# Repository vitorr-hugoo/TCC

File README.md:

# Estacao meteorologica — TCC

Este repositorio separa as fontes do produto, a documentacao duradoura e as
ferramentas de apoio. Arquivos gerados localmente ficam em `work/` e nao fazem
parte do historico Git.

| Area | Conteudo |
| --- | --- |
| `firmware/` | Firmware STM32, gateway ESP32, testes e configuracoes do produto. |
| `hardware/` | Projeto KiCad, bibliotecas locais e pacotes de fabricacao por versao. |
| `docs/` | Material do TCC, referencias e registros de engenharia. |
| `tools/` | Scripts reprodutiveis para hardware, documentos e automacao. |
| `work/` | Caches, renderizacoes e resultados locais descartaveis. |

Consulte os READMEs de cada area antes de alterar caminhos ou executar scripts.

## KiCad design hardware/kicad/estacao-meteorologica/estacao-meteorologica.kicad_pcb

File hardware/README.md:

# Hardware

O projeto principal esta em `kicad/estacao-meteorologica/`. Abra o arquivo
`estacao-meteorologica.kicad_pro` no KiCad. As folhas hierarquicas ficam em
`sheets/` e as bibliotecas locais do projeto ficam em `libraries/`.

As tabelas de simbolos e footprints usam caminhos relativos para
`../../libraries`, de modo que o projeto permanece portatil apos o clone.
`kicad/legacy/` preserva folhas antigas que nao fazem parte da hierarquia ativa.
Pacotes de fabricacao aprovados devem ser organizados por versao em `releases/`.

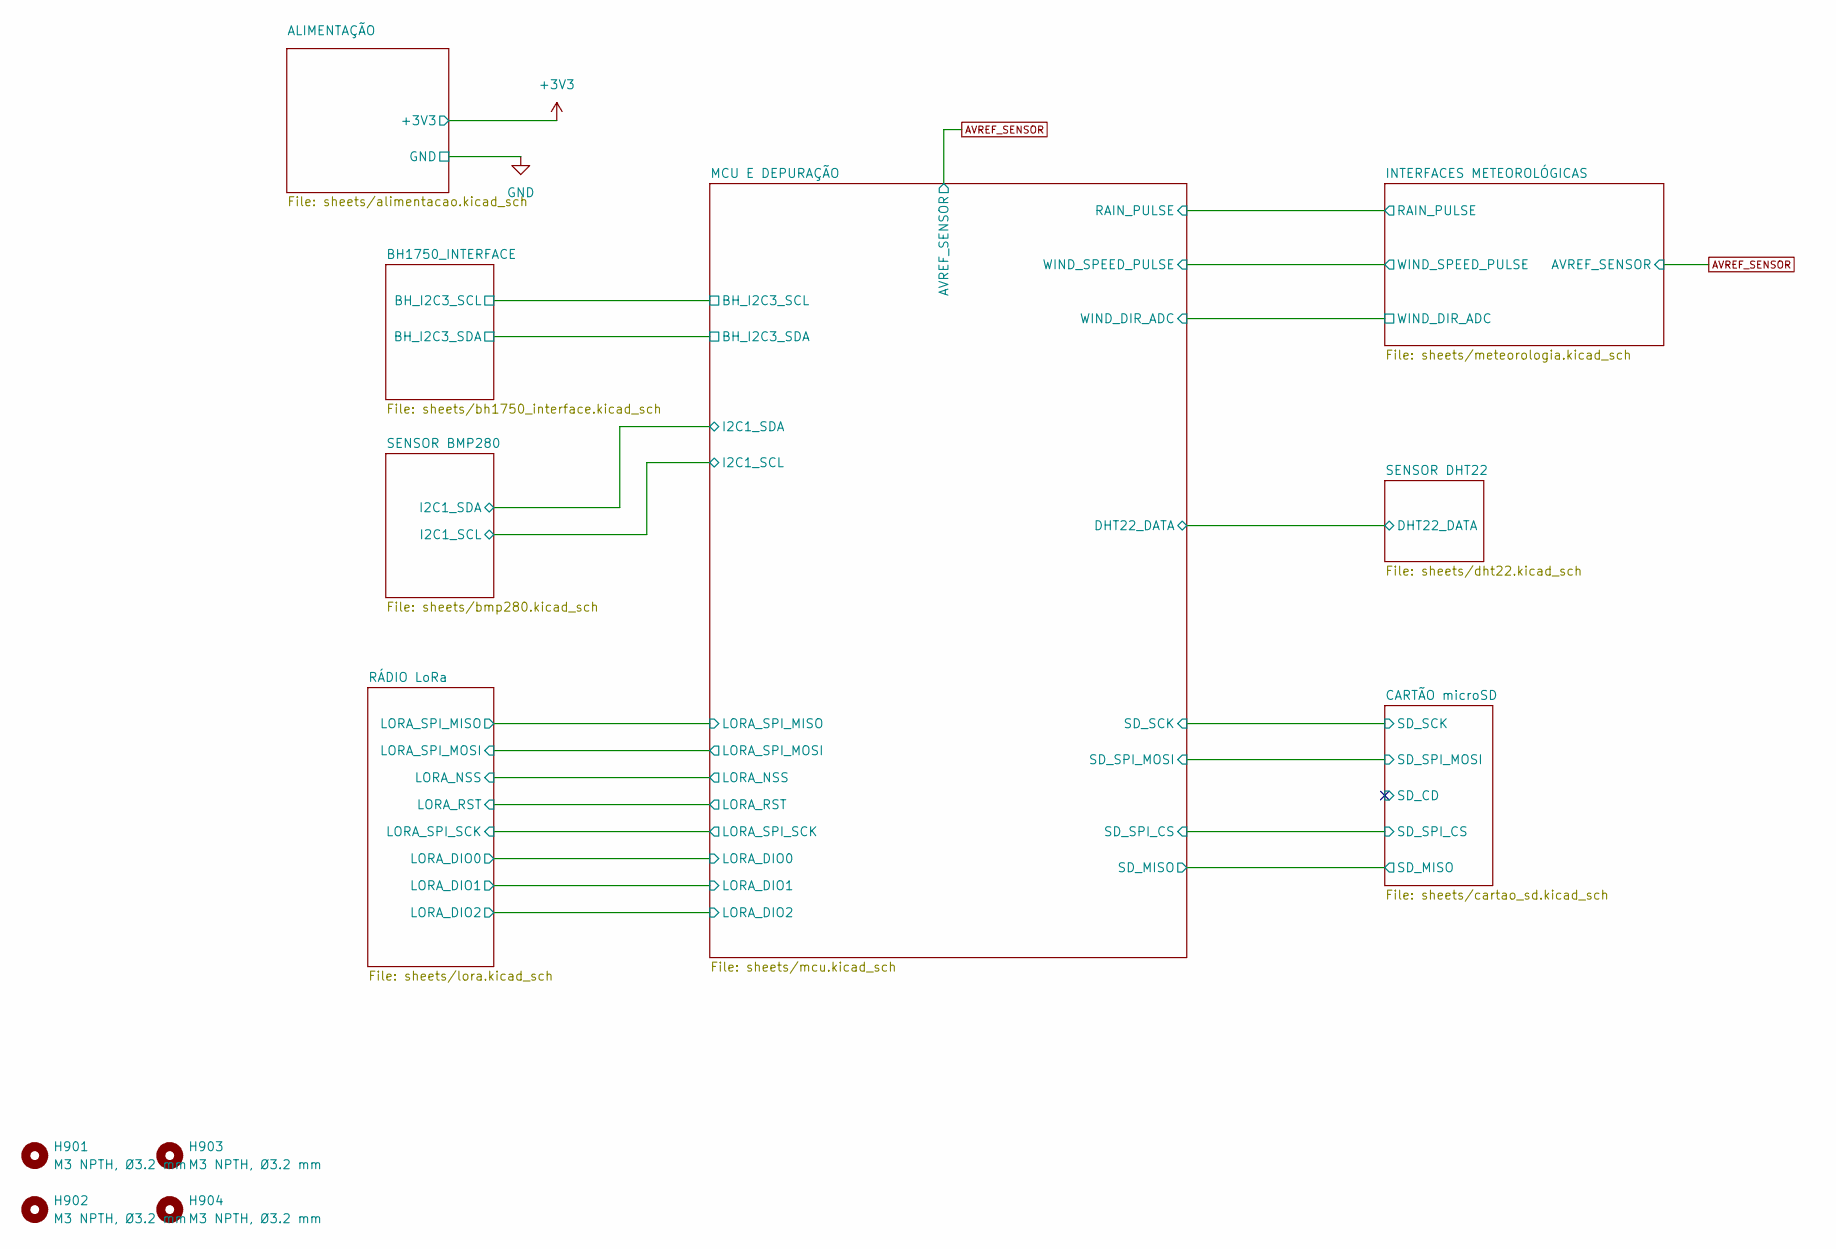
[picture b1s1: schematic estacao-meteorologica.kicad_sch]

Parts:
H901, H902, H903, H904: M3 NPTH, Ø3.2 mm; MountingHole_3.2mm_M3; MPN N/A — recurso mecânico da PCB; LCSC N/A

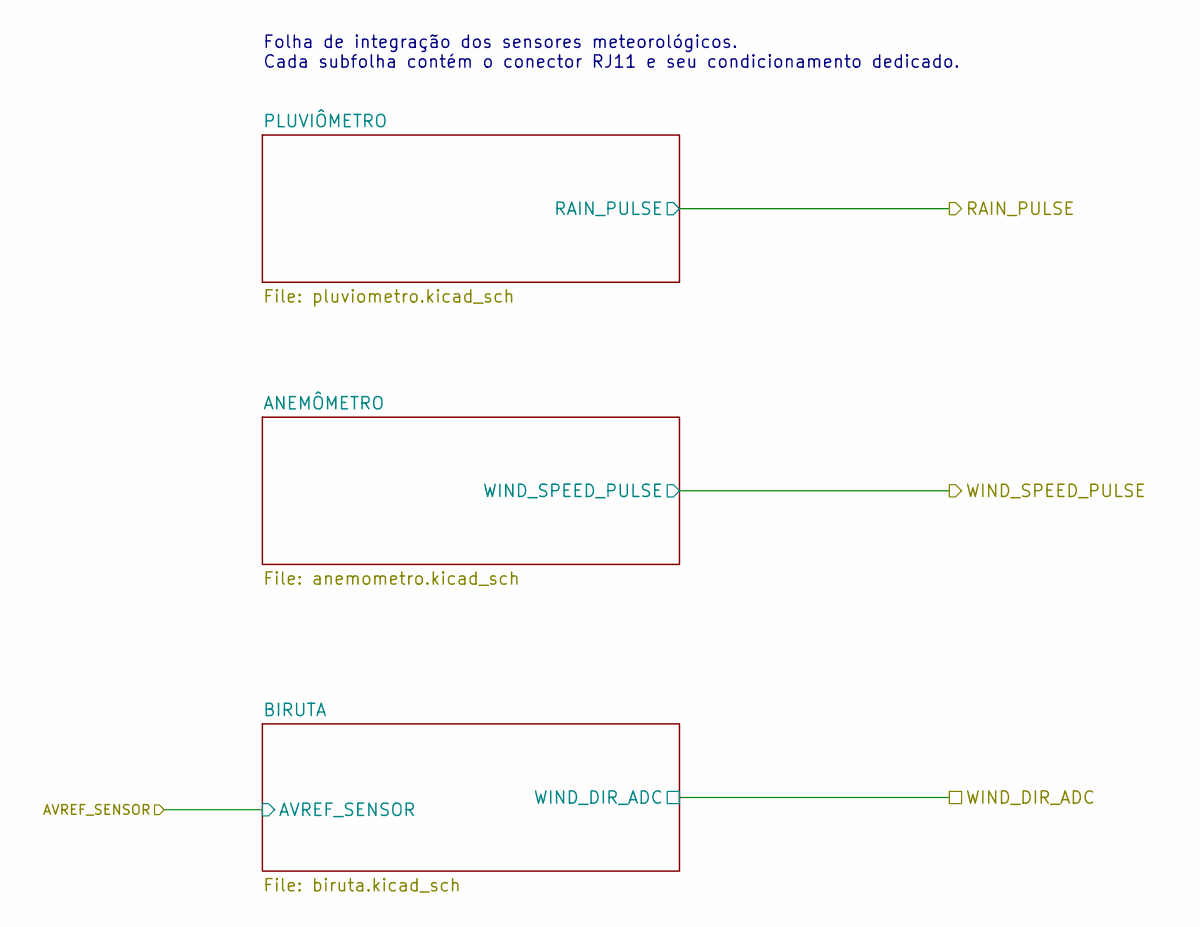
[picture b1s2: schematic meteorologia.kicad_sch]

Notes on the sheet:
Folha de integração dos sensores meteorológicos. Cada subfolha contém o conector RJ11 e seu condicionamento dedicado.

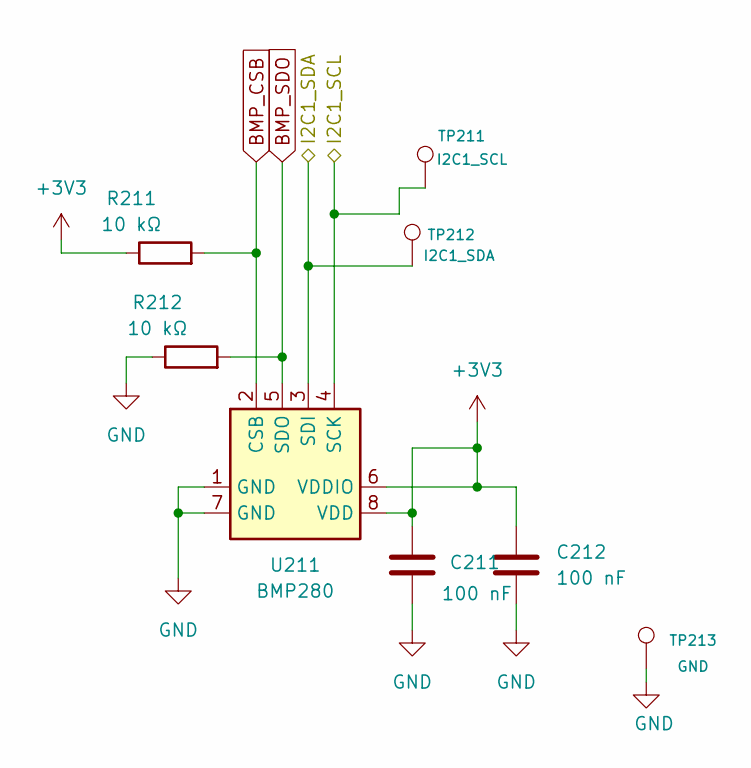
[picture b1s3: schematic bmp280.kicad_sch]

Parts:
C211, C212: 100 nF; C_0603_1608Metric; MPN CC0603KRX7R9BB104; LCSC C14663
R211, R212: 10 kΩ; R_0603_1608Metric; MPN 0603WAF1002T5E; LCSC C25804
TP211: I2C1_SCL; TestPoint_Pad_D1.0mm; MPN N/A - elemento de cobre da PCB; LCSC N/A
TP212: I2C1_SDA; TestPoint_Pad_D1.0mm; MPN N/A - elemento de cobre da PCB; LCSC N/A
TP213: GND; TestPoint_Pad_D1.0mm; MPN N/A - elemento de cobre da PCB; LCSC N/A
U211: BMP280; Bosch_LGA-8_2x2.5mm_P0.65mm_ClockwisePinNumbering; MPN BMP280; LCSC C83291

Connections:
+3V3: C211.1, C212.1, R211.1, U211.6 (VDDIO), U211.8 (VDD); also elsewhere on the board
/MCU E DEPURAÇÃO/I2C1_SCL: TP211.1, U211.4 (SCK); also elsewhere on the board
/MCU E DEPURAÇÃO/I2C1_SDA: TP212.1, U211.3 (SDI); also elsewhere on the board
BMP_CSB: R211.2, U211.2 (CSB)
BMP_SDO: R212.2, U211.5 (SDO)
GND: C211.2, C212.2, R212.1, TP213.1, U211.1 (GND), U211.7 (GND); also elsewhere on the board

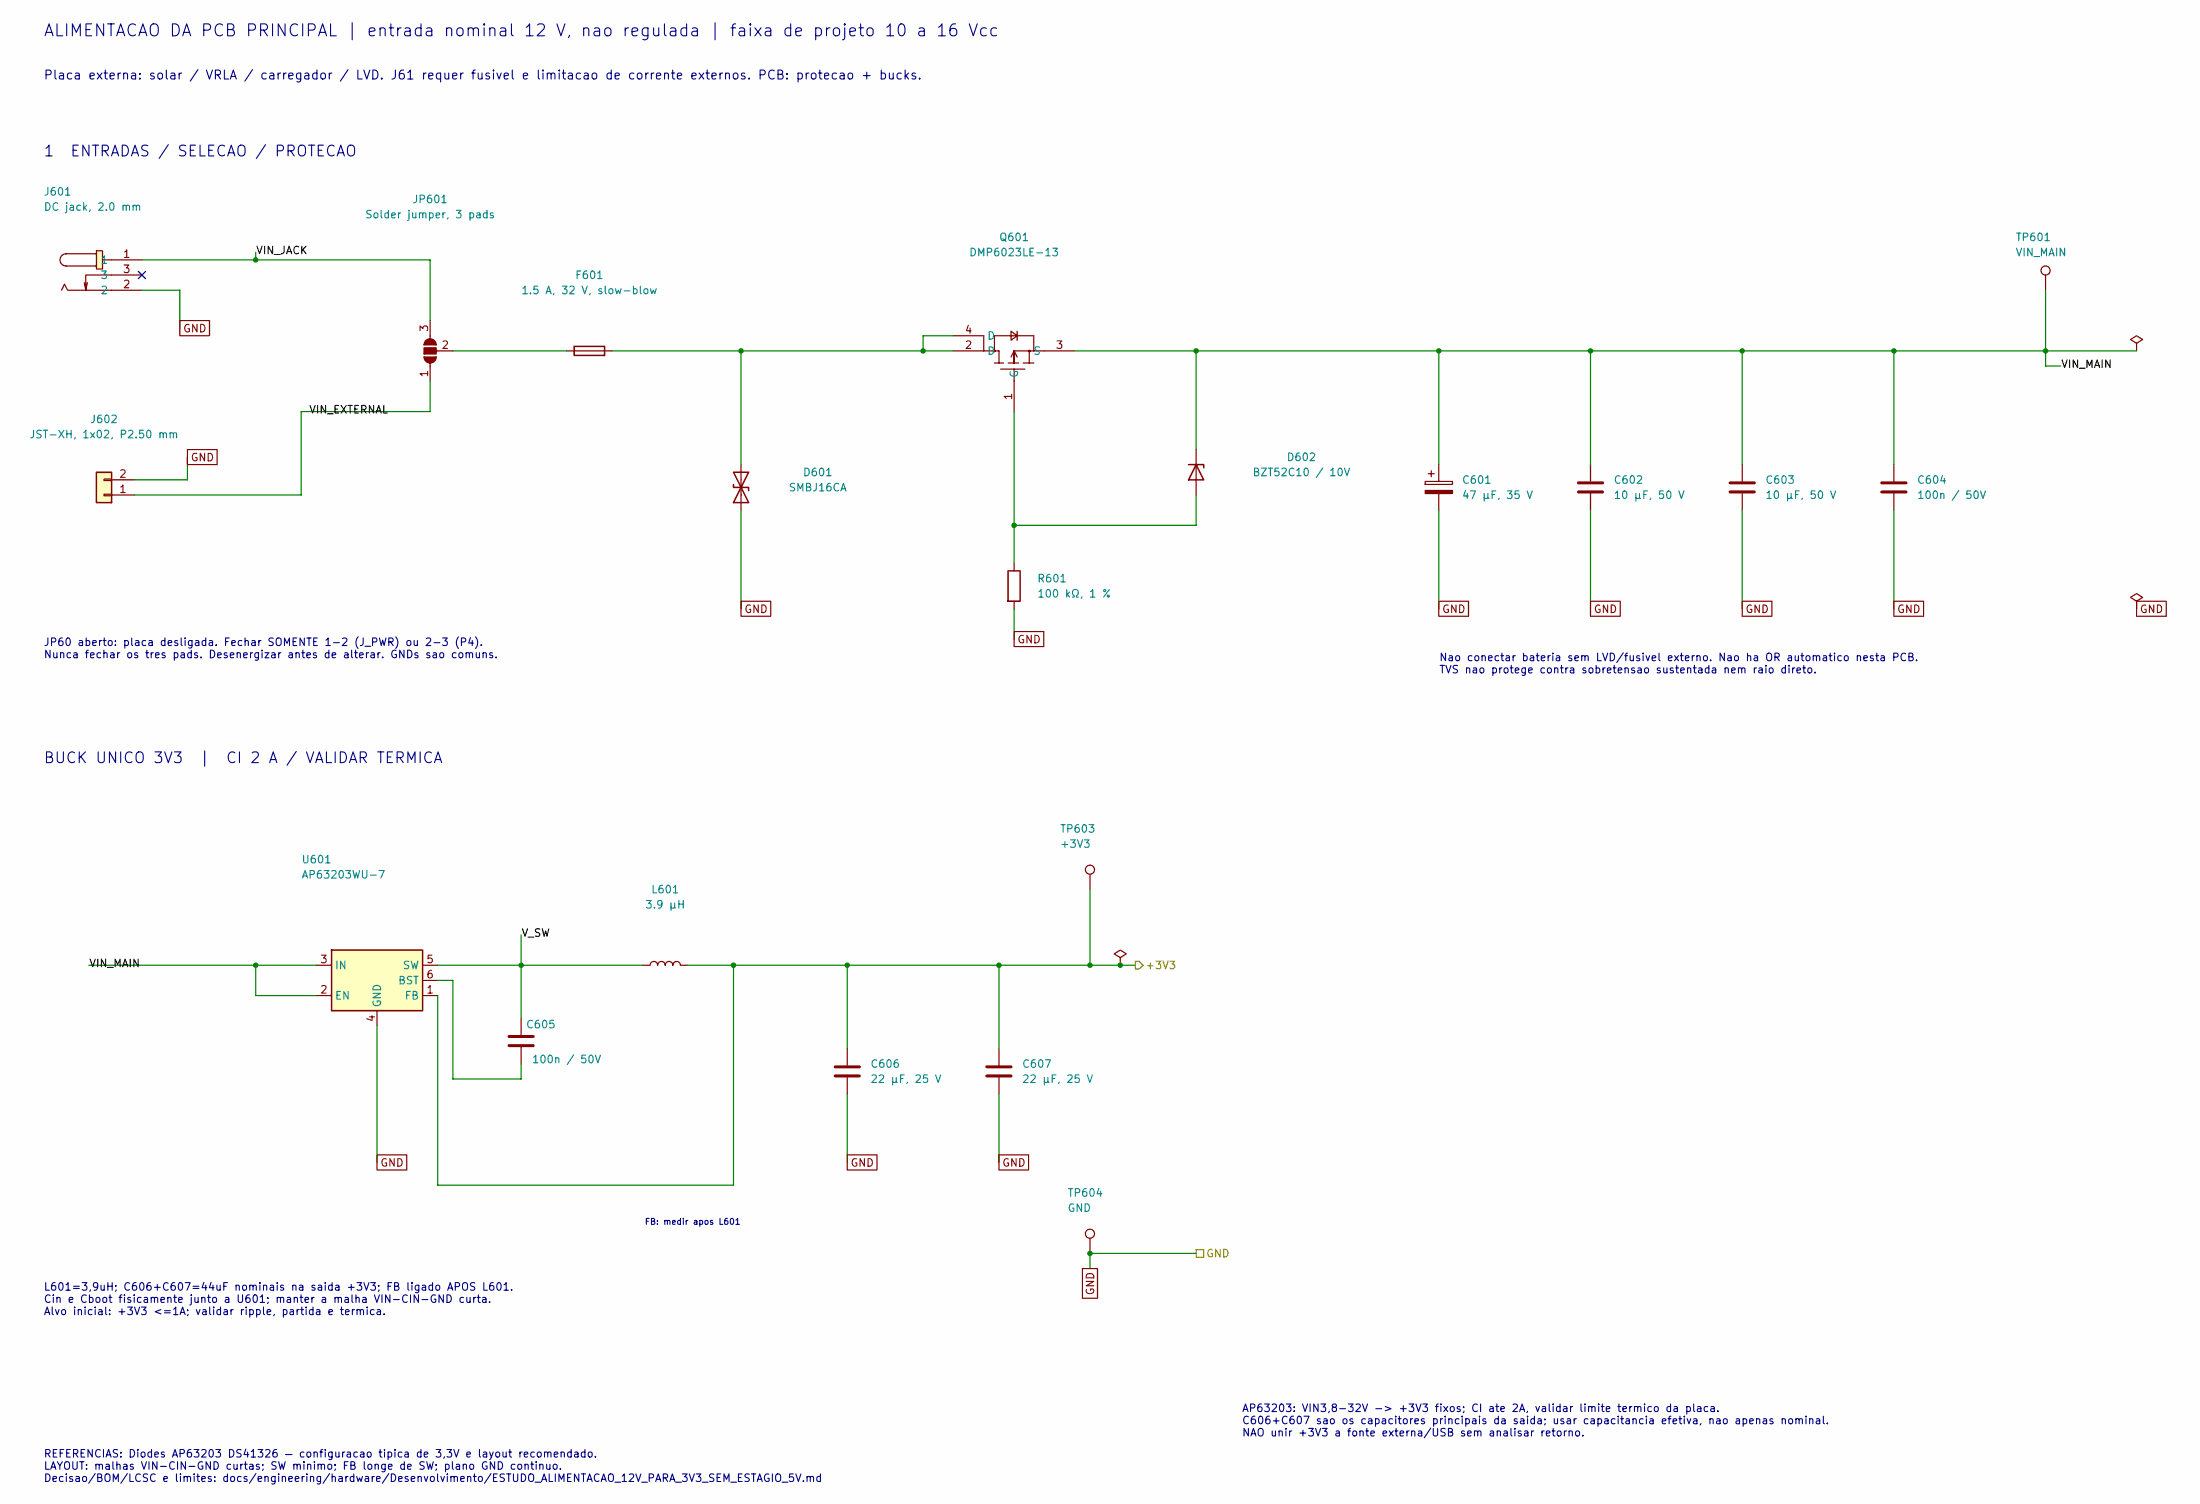
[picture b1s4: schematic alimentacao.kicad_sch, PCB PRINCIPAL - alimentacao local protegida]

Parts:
C601: 47 µF, 35 V; CP_Elec_6.3x5.8; MPN UWT1V470MCL1GS; LCSC C87068
C602, C603: 10 µF, 50 V; C_1206_3216Metric; MPN CL31A106KBHNNNE; LCSC C13585
C604, C605: 100n / 50V; C_0603_1608Metric; MPN CC0603KRX7R9BB104; LCSC C14663
C606, C607: 22 µF, 25 V; C_1206_3216Metric; MPN CL31A226KAHNNNE; LCSC C12891
D601: SMBJ16CA; D_SMB; MPN SMBJ16CA; LCSC C3001977
D602: BZT52C10 / 10V; D_SOD-123; MPN BZT52C10; LCSC C19077408
F601: 1.5 A, 32 V, slow-blow; Fuse_1206_3216Metric; MPN S1206-S-1.5A; LCSC C553929
J601: DC jack, 2.0 mm; DC-IN-TH_DC-005-2.0_C22459640; MPN DC-005-2.0; LCSC C22459640
J602: JST-XH, 1x02, P2.50 mm; JST_XH_B2B-XH-A_1x02_P2.50mm_Vertical; MPN B2B-XH-A(LF)(SN); LCSC C158012
JP601: Solder jumper, 3 pads; SolderJumper-3_P2.0mm_Open_TrianglePad1.0x1.5mm_NumberLabels; MPN N/A - elemento de cobre da PCB; LCSC N/A
L601: 3.9 µH; L_APV_ANR5040; MPN ANR5040T3R9M; LCSC C7427132
Q601: DMP6023LE-13; SOT-223-4_L6.5-W3.5-P2.30-LS7.0-BR; MPN DMP6023LE-13; LCSC C154901
R601: 100 kΩ, 1 %; R_0603_1608Metric; MPN 0603WAF1003T5E; LCSC C25803
TP601: VIN_MAIN; TestPoint_Pad_D1.0mm; MPN N/A - elemento de cobre da PCB; LCSC N/A
TP603: +3V3; TestPoint_Pad_D1.0mm; MPN N/A - elemento de cobre da PCB; LCSC N/A
TP604: GND; TestPoint_Pad_D1.0mm; MPN N/A - elemento de cobre da PCB; LCSC N/A
U601: AP63203WU-7; TSOT-23-6; MPN AP63203WU-7; LCSC C780769

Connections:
+3V3: C606.1, C607.1, L601.2, TP603.1, U601.1 (FB); also elsewhere on the board
/ALIMENTAÇÃO/VIN_EXTERNAL: J602.1, JP601.1 (A)
/ALIMENTAÇÃO/VIN_JACK: J601.1, JP601.3 (B)
/ALIMENTAÇÃO/VIN_MAIN: C601.1, C602.1, C603.1, C604.1, D602.1 (K), Q601.3 (S), TP601.1, U601.2 (EN), U601.3 (IN)
/ALIMENTAÇÃO/V_SW: C605.2, L601.1, U601.5 (SW)
GND: C601.2, C602.2, C603.2, C604.2, C606.2, C607.2, D601.1 (A1), J601.2, J602.2, R601.2, TP604.1, U601.4 (GND); also elsewhere on the board
unnamed: D601.2 (A2), F601.2, Q601.2 (D), Q601.4 (D)
unnamed: D602.2 (A), Q601.1 (G), R601.1
unnamed: F601.1, JP601.2 (C)
unnamed: C605.1, U601.6 (BST)

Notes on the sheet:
ALIMENTACAO DA PCB PRINCIPAL | entrada nominal 12 V, nao regulada | faixa de projeto 10 a 16 Vcc
L601=3,9uH; C606+C607=44uF nominais na saida +3V3; FB ligado APOS L601. Cin e Cboot fisicamente junto a U601; manter a malha VIN-CIN-GND curta. Alvo inicial: +3V3 <=1A; validar ripple, partida e termica.
AP63203: VIN3,8-32V -> +3V3 fixos; CI ate 2A, validar limite termico da placa. C606+C607 sao os capacitores principais da saida; usar capacitancia efetiva, nao apenas nominal. NAO unir +3V3 a fonte externa/USB sem analisar retorno.
Placa externa: solar / VRLA / carregador / LVD. J61 requer fusivel e limitacao de corrente externos. PCB: protecao + bucks.
1 ENTRADAS / SELECAO / PROTECAO
REFERENCIAS: Diodes AP63203 DS41326 — configuracao tipica de 3,3V e layout recomendado. LAYOUT: malhas VIN-CIN-GND curtas; SW minimo; FB longe de SW; plano GND continuo. Decisao/BOM/LCSC e limites: docs/engineering/hardware/Desenvolvimento/ESTUDO_ALIMENTACAO_12V_PARA_3V3_SEM_ESTAGIO_5V.md
JP60 aberto: placa desligada. Fechar SOMENTE 1-2 (J_PWR) ou 2-3 (P4). Nunca fechar os tres pads. Desenergizar antes de alterar. GNDs sao comuns.
Nao conectar bateria sem LVD/fusivel externo. Nao ha OR automatico nesta PCB. TVS nao protege contra sobretensao sustentada nem raio direto.
BUCK UNICO 3V3 | CI 2 A / VALIDAR TERMICA
FB: medir apos L601

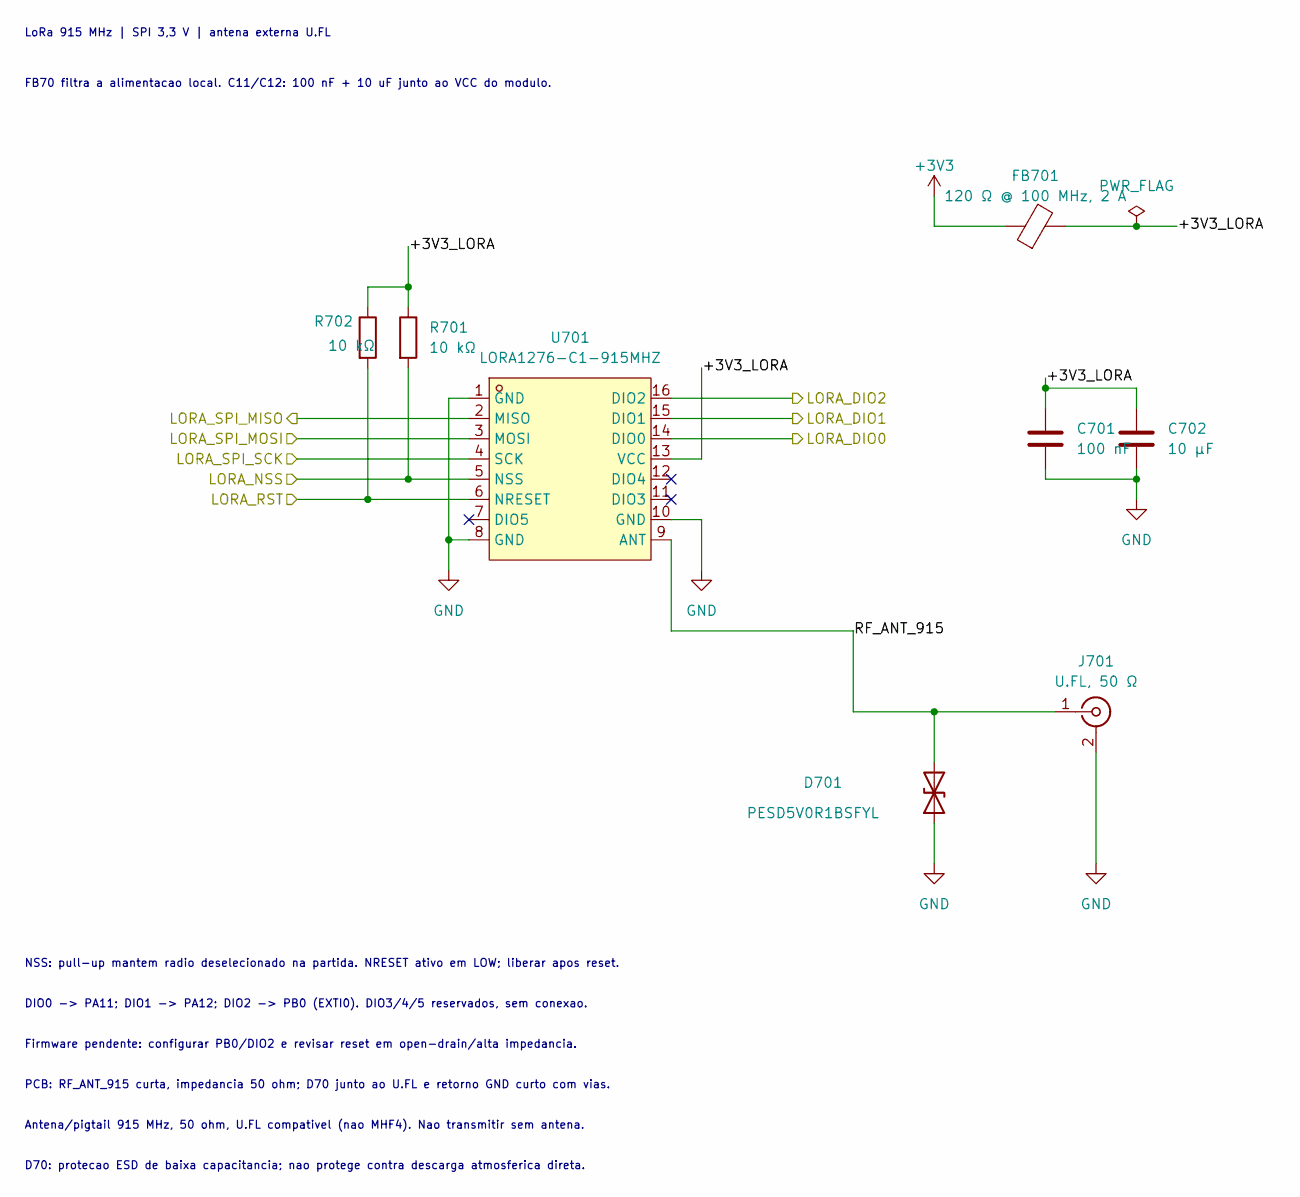
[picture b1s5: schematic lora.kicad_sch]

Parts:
C701: 100 nF; C_0603_1608Metric; MPN CC0603KRX7R9BB104; LCSC C14663
C702: 10 µF; C_1206_3216Metric; MPN CL31A106KBHNNNE; LCSC C13585
D701: PESD5V0R1BSFYL; SOD-962_L0.6-W0.3-BI; MPN PESD5V0R1BSFYL; LCSC C461221
FB701: 120 Ω @ 100 MHz, 2 A; L_0603_1608Metric; MPN BLM18PG121SN1D; LCSC C14709
J701: U.FL, 50 Ω; U.FL_Hirose_U.FL-R-SMT-1_Vertical; MPN U.FL-R-SMT-1(10); LCSC C88373
R701, R702: 10 kΩ; R_0603_1608Metric; MPN 0603WAF1002T5E; LCSC C25804
U701: LORA1276-C1-915MHZ; COMM-SMD_LORA1276-C1-915MHZ; MPN lora1276-C1-915MHz; LCSC C3001531

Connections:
+3V3: FB701.1; also elsewhere on the board
/MCU E DEPURAÇÃO/LORA_DIO0: U701.14 (DIO0); also elsewhere on the board
/MCU E DEPURAÇÃO/LORA_DIO1: U701.15 (DIO1); also elsewhere on the board
/MCU E DEPURAÇÃO/LORA_DIO2: U701.16 (DIO2); also elsewhere on the board
/MCU E DEPURAÇÃO/LORA_NSS: R701.2, U701.5 (NSS); also elsewhere on the board
/MCU E DEPURAÇÃO/LORA_RST: R702.2, U701.6 (NRESET); also elsewhere on the board
/MCU E DEPURAÇÃO/LORA_SPI_MISO: U701.2 (MISO); also elsewhere on the board
/MCU E DEPURAÇÃO/LORA_SPI_MOSI: U701.3 (MOSI); also elsewhere on the board
/MCU E DEPURAÇÃO/LORA_SPI_SCK: U701.4 (SCK); also elsewhere on the board
/RÁDIO LoRa/+3V3_LORA: C701.1, C702.1, FB701.2, R701.1, R702.1, U701.13 (VCC)
/RÁDIO LoRa/RF_ANT_915: D701.2 (A2), J701.1 (In), U701.9 (ANT)
GND: C701.2, C702.2, D701.1 (A1), J701.2 (Ext), U701.1 (GND), U701.8 (GND), U701.10 (GND); also elsewhere on the board

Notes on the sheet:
NSS: pull-up mantem radio deselecionado na partida. NRESET ativo em LOW; liberar apos reset.
DIO0 -> PA11; DIO1 -> PA12; DIO2 -> PB0 (EXTI0). DIO3/4/5 reservados, sem conexao.
LoRa 915 MHz | SPI 3,3 V | antena externa U.FL
D70: protecao ESD de baixa capacitancia; nao protege contra descarga atmosferica direta.
Antena/pigtail 915 MHz, 50 ohm, U.FL compativel (nao MHF4). Nao transmitir sem antena.
FB70 filtra a alimentacao local. C11/C12: 100 nF + 10 uF junto ao VCC do modulo.
Firmware pendente: configurar PB0/DIO2 e revisar reset em open-drain/alta impedancia.
PCB: RF_ANT_915 curta, impedancia 50 ohm; D70 junto ao U.FL e retorno GND curto com vias.

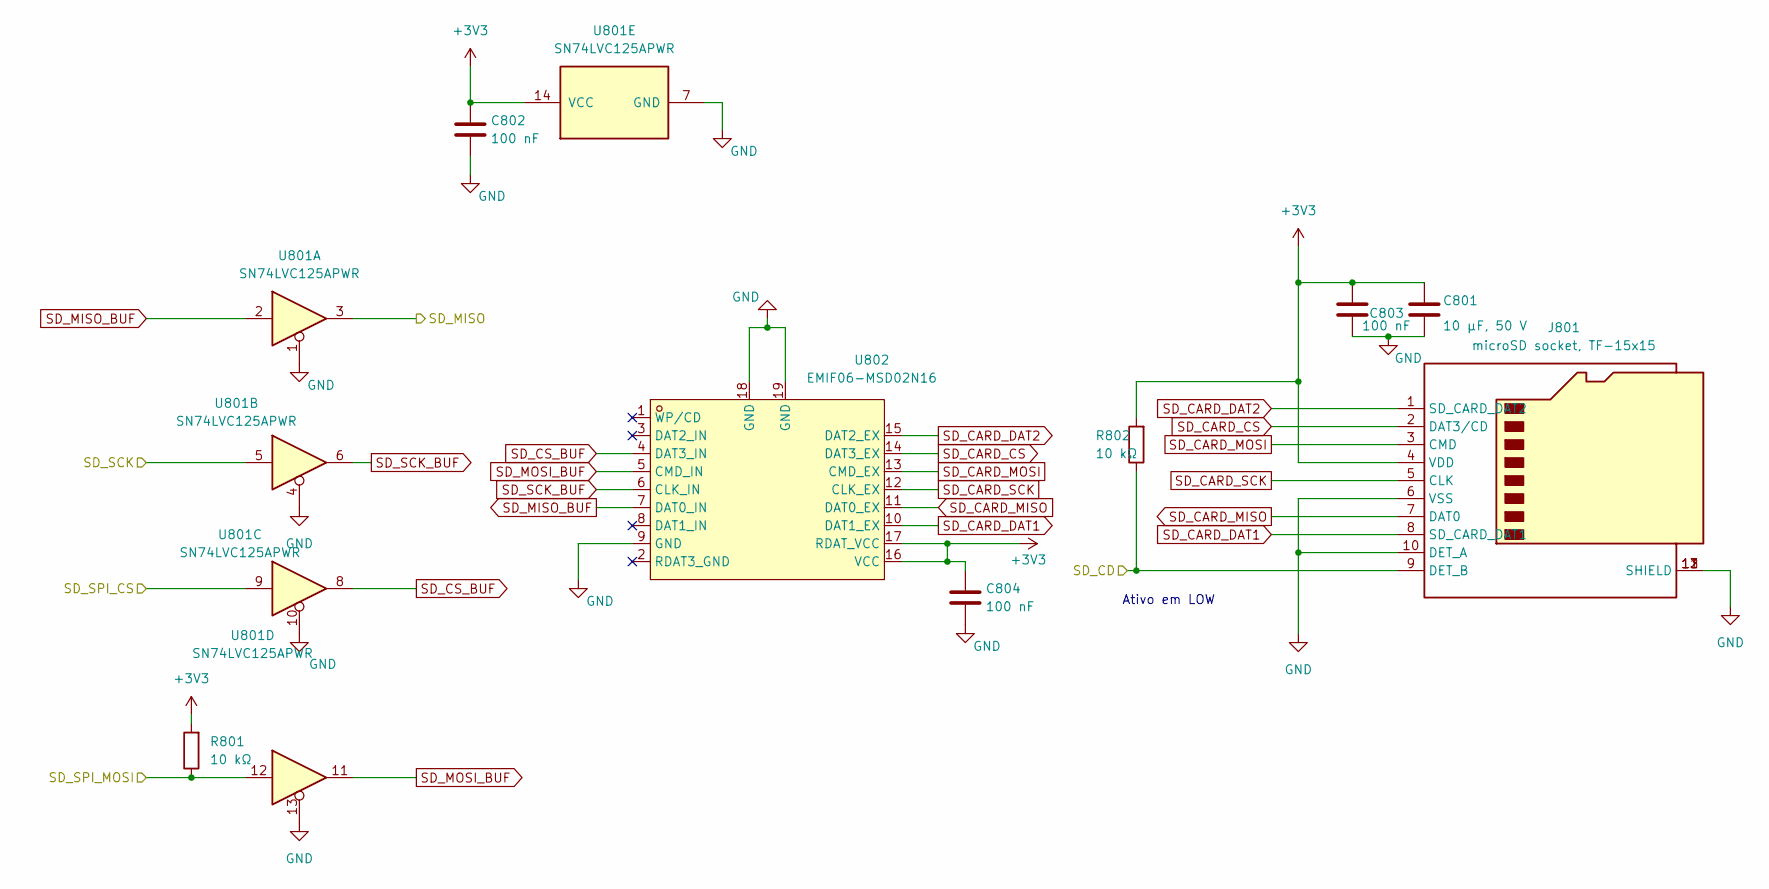
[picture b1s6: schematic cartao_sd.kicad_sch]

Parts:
C801: 10 µF, 50 V; C_1206_3216Metric; MPN CL31A106KBHNNNE; LCSC C13585
C802, C803, C804: 100 nF; C_0603_1608Metric; MPN CC0603KRX7R9BB104; LCSC C14663
J801: microSD socket, TF-15x15; microSD_SOFNG_TF-15x15_C111196; MPN TF-15x15; LCSC C111196
R801, R802: 10 kΩ; R_0603_1608Metric; MPN 0603WAF1002T5E; LCSC C25804
U801: SN74LVC125APWR; TSSOP-14_4.4x5mm_P0.65mm; MPN SN74LVC125APWR; LCSC C7813
U802: EMIF06-MSD02N16; QFN-16L_L3.5-W1.2-P0.40_EMIF06-MSD02N16; MPN EMIF06-MSD02N16; LCSC C5267594

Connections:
+3V3: C801.1, C802.1, C803.1, C804.1, J801.4 (VDD), R801.2, R802.2, U801.14 (VCC), U802.16 (VCC), U802.17 (RDAT_VCC); also elsewhere on the board
/CARTÃO microSD/SD_CD: J801.9 (DET_B), R802.1
/CARTÃO microSD/SD_MISO: U801.3; also elsewhere on the board
/CARTÃO microSD/SD_SCK: U801.5; also elsewhere on the board
/CARTÃO microSD/SD_SPI_CS: U801.9; also elsewhere on the board
/CARTÃO microSD/SD_SPI_MOSI: R801.1, U801.12; also elsewhere on the board
GND: C801.2, C802.2, C803.2, C804.2, J801.6 (VSS), J801.10 (DET_A), J801.11 (SHIELD), J801.12 (SHIELD), J801.13 (SHIELD), U801.1, U801.4, U801.7 (GND), U801.10, U801.13, U802.9 (GND), U802.18 (GND), U802.19 (GND); also elsewhere on the board
SD_CARD_CS: J801.2 (DAT3/CD), U802.14 (DAT3_EX)
SD_CARD_DAT1: J801.8 (SD_CARD_DAT1), U802.10 (DAT1_EX)
SD_CARD_DAT2: J801.1 (SD_CARD_DAT2), U802.15 (DAT2_EX)
SD_CARD_MISO: J801.7 (DAT0), U802.11 (DAT0_EX)
SD_CARD_MOSI: J801.3 (CMD), U802.13 (CMD_EX)
SD_CARD_SCK: J801.5 (CLK), U802.12 (CLK_EX)
SD_CS_BUF: U801.8, U802.4 (DAT3_IN)
SD_MISO_BUF: U801.2, U802.7 (DAT0_IN)
SD_MOSI_BUF: U801.11, U802.5 (CMD_IN)
SD_SCK_BUF: U801.6, U802.6 (CLK_IN)

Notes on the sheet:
Ativo em LOW

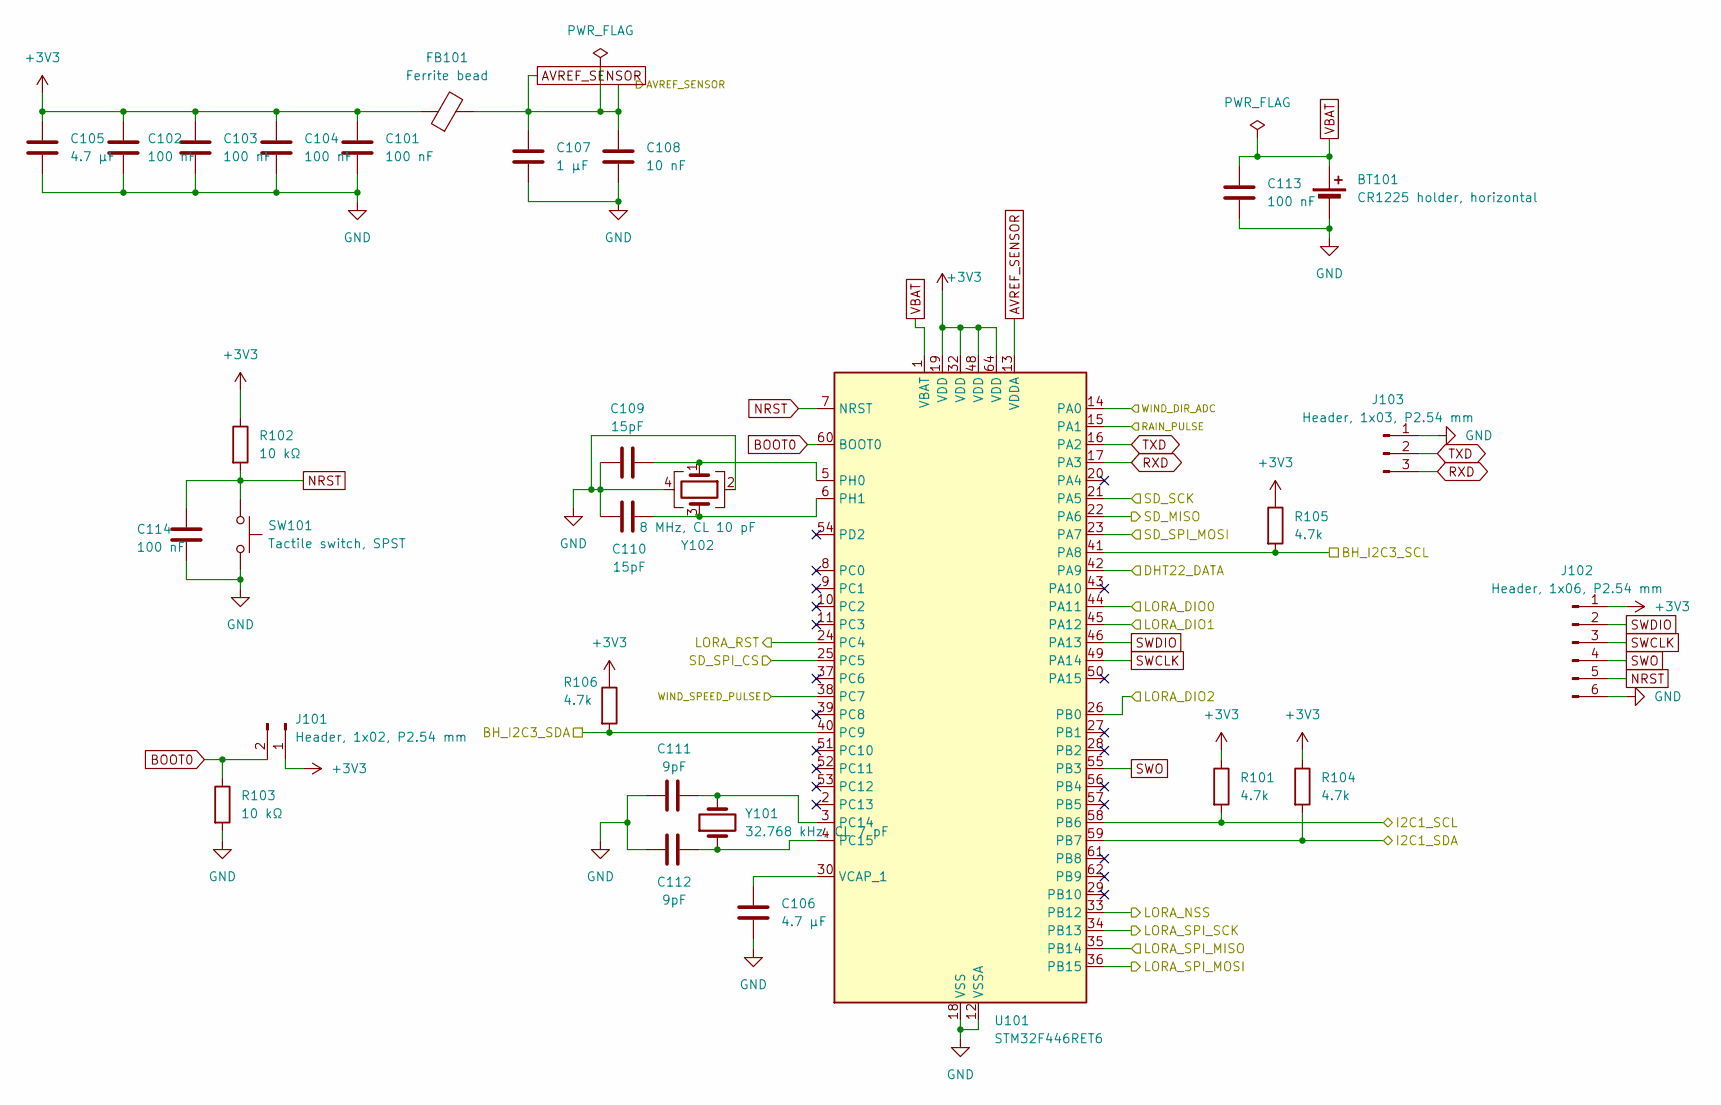
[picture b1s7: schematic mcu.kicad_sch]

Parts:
BT101: CR1225 holder, horizontal; BT_Holder_MYOUNG_BS-12-B4AK025-R; MPN BS-12-B4AK025-R; LCSC C20606807
C101, C102, C103, C104, C113, C114: 100 nF; C_0603_1608Metric; MPN CC0603KRX7R9BB104; LCSC C14663
C105, C106: 4.7 µF; C_0805_2012Metric; MPN MSAST21GAB5475MTNA01; LCSC C7307475
C107: 1 µF; C_0603_1608Metric; MPN CS1608X7R105K250NRB; LCSC C513775
C108: 10 nF; C_0603_1608Metric; MPN 0603B103K500NT; LCSC C57112
C109, C110: 15pF; C_0603_1608Metric; MPN CC0603JRNPO9BN150; LCSC C107037
C111, C112: 9pF; C_0603_1608Metric; MPN AC0603DRNPO9BN9R0; LCSC C3877909
FB101: Ferrite bead; L_0603_1608Metric; MPN BLM18PG121SN1D; LCSC C14709
J101: Header, 1x02, P2.54 mm; PinHeader_1x02_P2.54mm_Vertical; MPN PZ254V-11-02P; LCSC C492401
J102: Header, 1x06, P2.54 mm; PinHeader_1x06_P2.54mm_Vertical; MPN PZ254V-11-06P; LCSC C492405
J103: Header, 1x03, P2.54 mm; PinHeader_1x03_P2.54mm_Vertical; MPN PZ254V-11-03P; LCSC C492402
R101, R104, R105, R106: 4.7k; R_0603_1608Metric; MPN 0603WAF4701T5E; LCSC C23162
R102, R103: 10 kΩ; R_0603_1608Metric; MPN 0603WAF1002T5E; LCSC C25804
SW101: Tactile switch, SPST; SW_SPST_TL3342; MPN TL3342F160QG; LCSC C2886898
U101: STM32F446RET6; LQFP-64_10x10mm_P0.5mm; MPN STM32F446RET6; LCSC C69336
Y101: 32.768 kHz, CL 7 pF; Crystal_SMD_3215-2Pin_3.2x1.5mm; MPN 7LC32768F07UC; LCSC C252399
Y102: 8 MHz, CL 10 pF; Crystal_SMD_3225-4Pin_3.2x2.5mm; MPN 3225-8.00-10-10-10/A; LCSC C518154

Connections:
+3V3: C101.1, C102.1, C103.1, C104.1, C105.1, FB101.1, J101.1, J102.1, R101.1, R102.1, R104.1, R105.1, R106.1, U101.19 (VDD), U101.32 (VDD), U101.48 (VDD), U101.64 (VDD); also elsewhere on the board
/BH1750_INTERFACE/BH_I2C3_SCL: R105.2, U101.41 (PA8); also elsewhere on the board
/BH1750_INTERFACE/BH_I2C3_SDA: R106.2, U101.40 (PC9); also elsewhere on the board
/CARTÃO microSD/SD_MISO: U101.22 (PA6); also elsewhere on the board
/CARTÃO microSD/SD_SCK: U101.21 (PA5); also elsewhere on the board
/CARTÃO microSD/SD_SPI_CS: U101.25 (PC5); also elsewhere on the board
/CARTÃO microSD/SD_SPI_MOSI: U101.23 (PA7); also elsewhere on the board
/INTERFACES METEOROLÓGICAS/RAIN_PULSE: U101.15 (PA1); also elsewhere on the board
/INTERFACES METEOROLÓGICAS/WIND_DIR_ADC: U101.14 (PA0); also elsewhere on the board
/INTERFACES METEOROLÓGICAS/WIND_SPEED_PULSE: U101.38 (PC7); also elsewhere on the board
/MCU E DEPURAÇÃO/DHT22_DATA: U101.42 (PA9); also elsewhere on the board
/MCU E DEPURAÇÃO/I2C1_SCL: R101.2, U101.58 (PB6); also elsewhere on the board
/MCU E DEPURAÇÃO/I2C1_SDA: R104.2, U101.59 (PB7); also elsewhere on the board
/MCU E DEPURAÇÃO/LORA_DIO0: U101.44 (PA11); also elsewhere on the board
/MCU E DEPURAÇÃO/LORA_DIO1: U101.45 (PA12); also elsewhere on the board
/MCU E DEPURAÇÃO/LORA_DIO2: U101.26 (PB0); also elsewhere on the board
/MCU E DEPURAÇÃO/LORA_NSS: U101.33 (PB12); also elsewhere on the board
/MCU E DEPURAÇÃO/LORA_RST: U101.24 (PC4); also elsewhere on the board
/MCU E DEPURAÇÃO/LORA_SPI_MISO: U101.35 (PB14); also elsewhere on the board
/MCU E DEPURAÇÃO/LORA_SPI_MOSI: U101.36 (PB15); also elsewhere on the board
/MCU E DEPURAÇÃO/LORA_SPI_SCK: U101.34 (PB13); also elsewhere on the board
AVREF_SENSOR: C107.1, C108.1, FB101.2, U101.13 (VDDA); also elsewhere on the board
BOOT0: J101.2, R103.1, U101.60 (BOOT0)
GND: BT101.2 (-), C101.2, C102.2, C103.2, C104.2, C105.2, C106.2, C107.2, C108.2, C109.1, C110.1, C111.1, C112.1, C113.2, C114.2, J102.6, J103.1, R103.2, SW101.2, U101.12 (VSSA), U101.18 (VSS), U101.31 (VSS), U101.47 (VSS), U101.63 (VSS), Y102.2, Y102.4; also elsewhere on the board
NRST: C114.1, J102.5, R102.2, SW101.1, U101.7 (NRST)
unnamed: C111.2, U101.3 (PC14), Y101.2
unnamed: C112.2, U101.4 (PC15), Y101.1
unnamed: C109.2, U101.5 (PH0), Y102.1
unnamed: C110.2, U101.6 (PH1), Y102.3
unnamed: C106.1, U101.30 (VCAP_1)
RXD: J103.3, U101.17 (PA3)
SWCLK: J102.3, U101.49 (PA14)
SWDIO: J102.2, U101.46 (PA13)
SWO: J102.4, U101.55 (PB3)
TXD: J103.2, U101.16 (PA2)
VBAT: BT101.1 (+), C113.1, U101.1 (VBAT)

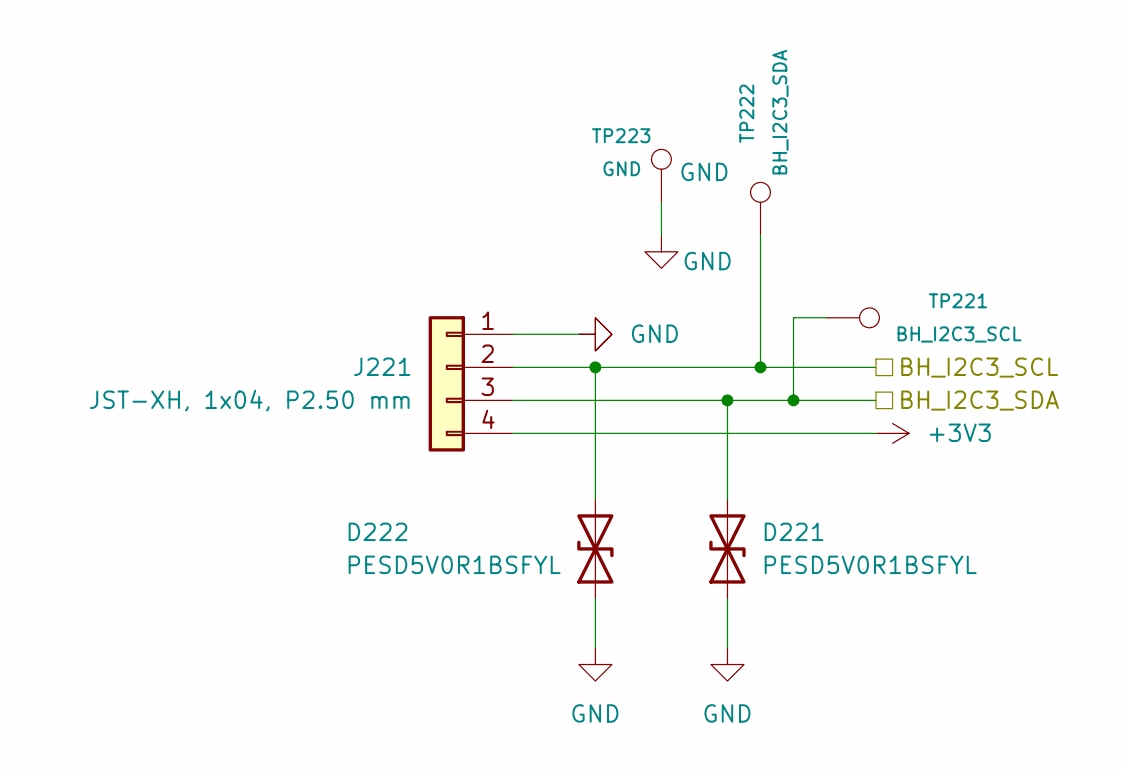
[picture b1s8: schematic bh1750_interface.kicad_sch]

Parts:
D221, D222: PESD5V0R1BSFYL; SOD-962_L0.6-W0.3-BI; MPN PESD5V0R1BSFYL; LCSC C461221
J221: JST-XH, 1x04, P2.50 mm; JST_XH_B4B-XH-A_1x04_P2.50mm_Vertical; MPN B4B-XH-A(LF)(SN); LCSC C144395
TP221: BH_I2C3_SCL; TestPoint_Pad_D1.0mm; MPN N/A - elemento de cobre da PCB; LCSC N/A
TP222: BH_I2C3_SDA; TestPoint_Pad_D1.0mm; MPN N/A - elemento de cobre da PCB; LCSC N/A
TP223: GND; TestPoint_Pad_D1.0mm; MPN N/A - elemento de cobre da PCB; LCSC N/A

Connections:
+3V3: J221.4; also elsewhere on the board
/BH1750_INTERFACE/BH_I2C3_SCL: D222.2 (A2), J221.2, TP222.1; also elsewhere on the board
/BH1750_INTERFACE/BH_I2C3_SDA: D221.2 (A2), J221.3, TP221.1; also elsewhere on the board
GND: D221.1 (A1), D222.1 (A1), J221.1, TP223.1; also elsewhere on the board

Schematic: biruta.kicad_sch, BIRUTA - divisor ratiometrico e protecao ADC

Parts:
C501: 100 nF; C_0603_1608Metric; MPN CC0603KRX7R9BB104; LCSC C14663
D501: PESD5V0S1UL; D_SOD-882; MPN PESD5V0S1UL,315; LCSC C85402
D502: BAS70-04; SOT-23; MPN BAS70-04,215; LCSC C389351
J501: RJ11 6P6C, 90°; RJ11-TH_PCB-6P6C-90; MPN R-RJ11R06P-A800; LCSC C189750
R1, R503: 1 kΩ; R_0603_1608Metric; MPN 0603WAF1001T5E; LCSC C21190
R501, R502: 10 kΩ; R_0603_1608Metric; MPN 0603WAF1002T5E; LCSC C25804
TP501: SENS_WIND_DIR_RAW; TestPoint_Pad_D1.0mm; MPN N/A - elemento de cobre da PCB; LCSC N/A
TP502: WIND_DIR_ADC; TestPoint_Pad_D1.0mm; MPN N/A - elemento de cobre da PCB; LCSC N/A
TP503: AVREF_SENSOR; TestPoint_Pad_D1.0mm; MPN N/A - elemento de cobre da PCB; LCSC N/A
TP504: GND; TestPoint_Pad_D1.0mm; MPN N/A - elemento de cobre da PCB; LCSC N/A

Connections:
+3V3: D502.2 (K), R1.2; also elsewhere on the board
/INTERFACES METEOROLÓGICAS/WIND_DIR_ADC: C501.1, R503.2, TP502.1; also elsewhere on the board
AVREF_SENSOR: R501.1, TP503.1; also elsewhere on the board
GND: C501.2, D501.2 (A), D502.1 (A), J501.5, TP504.1; also elsewhere on the board
unnamed: D501.1 (K), J501.2, R501.2, R502.1, TP501.1
unnamed: D502.3 (COM), R502.2, R503.1
unnamed: J501.3, R1.1
SENS_WIND_SPEED_RAW: J501.4; also elsewhere on the board

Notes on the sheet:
3 FILTRO / ADC
MISOL WH-SP-WD: rede resistiva passiva; 8 chaves / ate 16 codigos; cabo ~2 m. J32: p2=GND; p3=+3V3; p4=direcao do vento; p1/p5/p6=NC.
1 CONECTOR / DIVISOR
R50=10k 1%; ADC ideal=4095*R_sensor/(10000+R_sensor). R51/R52 estao APOS o divisor: nao entram na relacao DC ideal. Rfonte maxima ~20,23k; C50=100n: tau maxima ~2,02 ms; validar tempo ADC (144 ciclos).
2 LIMITACAO / CLAMP
AVREF_SENSOR deve vir de VDDA/AVDD do STM32, apos o filtro analogico; nao unir ao 3V3 digital por etiqueta. C50 junto ao PA0; retorno GND curto. Medir offsets por fuga e temperatura. A LUT ativa do firmware tem 16 entradas; 8 e o numero de amostras por leitura.

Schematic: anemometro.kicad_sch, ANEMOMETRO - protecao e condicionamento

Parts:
C401, C402: 100 nF; C_0603_1608Metric; MPN CC0603KRX7R9BB104; LCSC C14663
D401: PESD5V0S1UL; D_SOD-882; MPN PESD5V0S1UL,315; LCSC C85402
D402: BAS70-04; SOT-23; MPN BAS70-04,215; LCSC C389351
R401: 10 kΩ; R_0603_1608Metric; MPN 0603WAF1002T5E; LCSC C25804
R402: 4.7 kΩ; R_0603_1608Metric; MPN 0603WAF4701T5E; LCSC C23162
TP401: SENS_WIND_SPEED_RAW; TestPoint_Pad_D1.0mm; MPN N/A - elemento de cobre da PCB; LCSC N/A
TP402: SENS_WIND_SPEED_FILTERED; TestPoint_Pad_D1.0mm; MPN N/A - elemento de cobre da PCB; LCSC N/A
TP403: WIND_SPEED_PULSE; TestPoint_Pad_D1.0mm; MPN N/A - elemento de cobre da PCB; LCSC N/A
TP404: GND; TestPoint_Pad_D1.0mm; MPN N/A - elemento de cobre da PCB; LCSC N/A
U401: SN74LVC1G17DBVR; SOT-23-5; MPN SN74LVC1G17DBVR; LCSC C7836

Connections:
+3V3: C402.1, D402.2 (K), U401.5 (VCC); also elsewhere on the board
/INTERFACES METEOROLÓGICAS/WIND_SPEED_PULSE: TP403.1, U401.4; also elsewhere on the board
GND: C401.2, C402.2, D401.2 (A), D402.1 (A), R401.1, TP404.1, U401.3 (GND); also elsewhere on the board
unnamed: C401.1, D402.3 (COM), R402.2, TP402.1, U401.2
SENS_WIND_SPEED_RAW: D401.1 (K), R401.2, R402.1, TP401.1; also elsewhere on the board

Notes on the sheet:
Interface do sensor: J31.3 fornece +3V3 atraves de R42=1k; o reed externo fecha entre p3 e p4. R40=10k e o pull-down: reed aberto = 0 V; reed fechado = ~3,0 V e saida alta. C40=100n: tau de subida ~0,56 ms e de descida ~1,47 ms. PENDENCIA DE FIRMWARE: usar EXTI na subida e sem pull interno; o codig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
MISOL: contato reed passivo; cabo externo ~2 m. J31 p3 = +3V3 via R42; J31 p4 = sinal.
2 FILTRO / CLAMP SECUNDARIO
3 SCHMITT / MCU
1 CONECTOR / ESD / REFERENCIA
D40 deve ficar junto ao RJ11; R41, D41 e C40 junto ao U40. Manter plano GND continuo e retorno curto para D40. D40 e a protecao primaria do cabo; D41 apenas limita o residuo no buffer. Sem isolamento ou qualificacao contra raios: validar transitorios em bancada.
